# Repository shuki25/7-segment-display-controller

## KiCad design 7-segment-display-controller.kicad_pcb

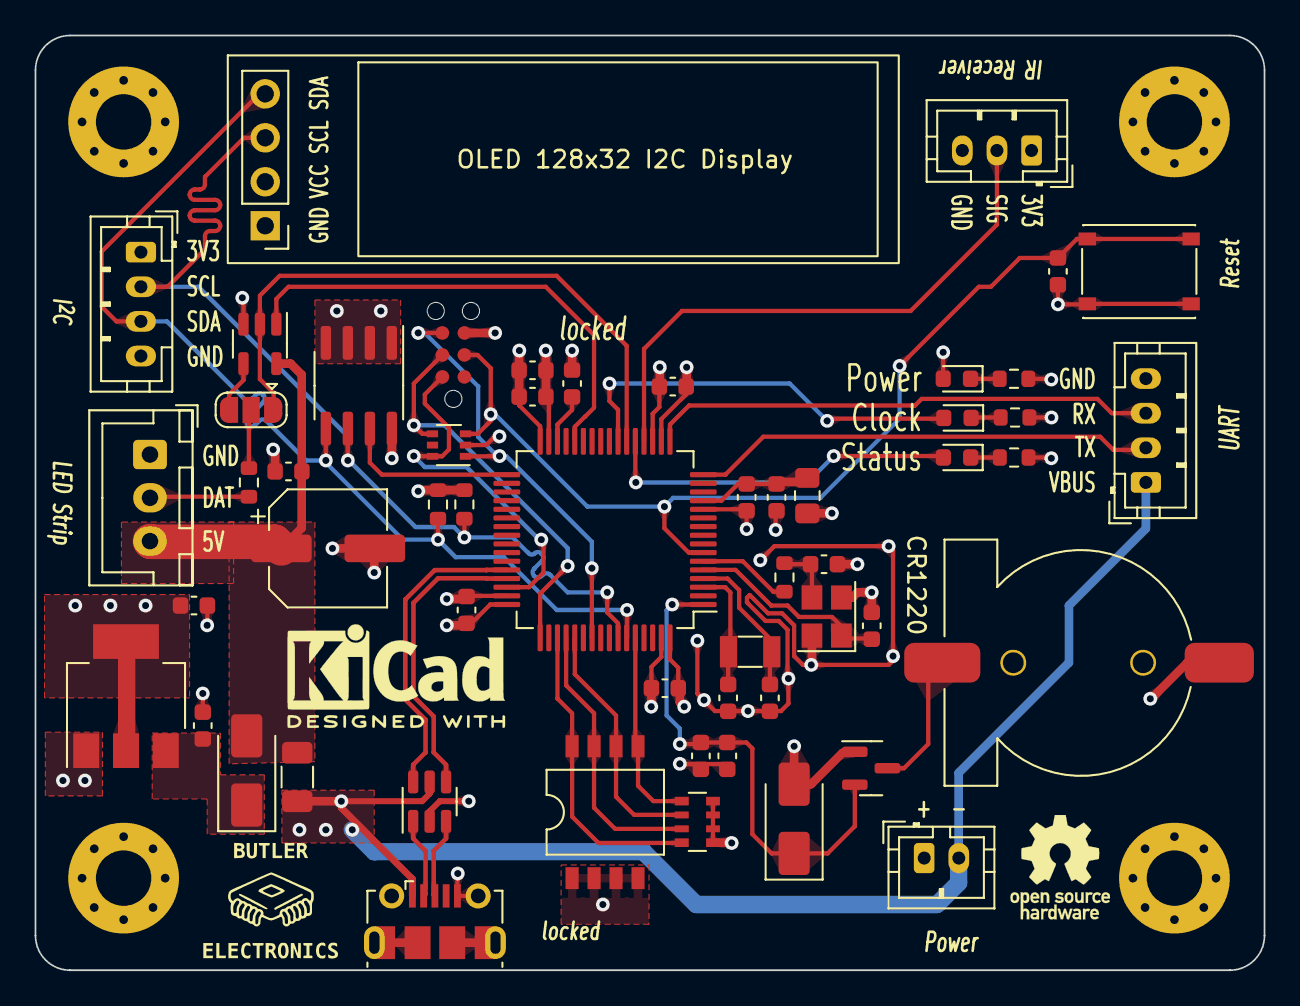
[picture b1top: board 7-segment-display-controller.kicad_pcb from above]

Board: 4 copper layers, 71.0 x 54.0 mm, 59 parts (0 on the bottom side), 42 nets.

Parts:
BT101: Battery_Cell; BatteryHolder_CR1220
C101, C107: 1uF; C_0603_1608Metric
C102, C117: 4.7uF; C_0603_1608Metric
C103, C104, C105, C106, C111, C114, C116, C118: 100nF; C_0603_1608Metric
C108, C109: 10pF; C_0603_1608Metric
C112, C113: 15pF; C_0603_1608Metric
C115: 470uF; CP_Elec_6.3x7.7
C201, C202: 22uF; C_0603_1608Metric
D101: GREEN; LED_0603_1608Metric
D102: RED; LED_0603_1608Metric
D103, D106: SS34; D_SMA
D104: SP0505BAJT; SOT-363_SC-70-6
D107: BLUE; LED_0603_1608Metric
F101: Polyfuse_Small; Fuse_1206_3216Metric
FB101: 600@100MHz; L_0805_2012Metric_Pad1.15x1.40mm_HandSolder
H101, H102, H103, H104: MountingHole; MountingHole_3.2mm_M3_Pad_Via
J101: Tag Connector; TC2030-IDC-NL
J102: USB_B_Micro; USB_Micro-B_Molex-105017-0001
J103, J105: JST 2.54 Header; JST_PH_B4B-PH-K_1x04_P2.00mm_Vertical
J104: JST 2.54 Header; JST_XH_B3B-XH-A_1x03_P2.50mm_Vertical
J106: JST 2.54 Header; JST_PH_B3B-PH-K_1x03_P2.00mm_Vertical
J107: Conn_01x02; JST_PH_B2B-PH-K_1x02_P2.00mm_Vertical
OLED101: OLED_I2C; OLED_128x32_I2C_4pins
Q101: AO3501A; SOT-23
R101, R105: 2K2; R_0603_1608Metric
R102, R109, R110: 1K5; R_0603_1608Metric
R103: 0; R_0603_1608Metric
R104: 330; R_0603_1608Metric
RN101: 10K; R_Array_Convex_4x0603
SW101: SW_DIP_x04; SMDIP-8_W6.6mm
SW106: SW_Push; XKB-Connectivity-TS-1187A-B-A-B
SW107: SW_SPDT; SolderJumper-3_P1.3mm_Open_RoundedPad1.0x1.5mm
U101: STM32F401RCTx; LQFP-64_10x10mm_P0.5mm
U102: USBLC6-2SC6; SOT-23-6
U103: 74AHCT1G125; SOT-23-5
U104: M24C64-RMN; SOIC-8_3.9x4.9mm_P1.27mm
U201: AMS1117-3.3; SOT-223-3_TabPin2
Y101: 16MHz; Crystal_SMD_3225-4Pin_3.2x2.5mm
Y103: 32.768kHz; Crystal_SMD_3215-2Pin_3.2x1.5mm

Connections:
+3.3VA: C106.1, C107.1, FB101.1, U101.13 (VREF+)
+3V3: C102.1, C103.1, C104.1, C105.1, C111.1, C202.2, D102.2 (A), D106.2 (A), FB101.2, J105.1, J106.1, OLED101.2 (VCC), Q101.1 (G), R109.2, R110.2, SW101.1, SW101.2, SW101.3, SW101.4, U101.19 (VDD), U101.32 (VDD), U101.48 (VDD), U101.64 (VDD), U104.8 (VCC), U201.2 (VO)
+5V: C115.1, C118.1, D103.2 (A), F101.2, J104.3, U103.5 (VCC)
/BAT+: BT101.1 (+), Q101.3 (D)
/BOOT0: RN101.5 (R4.2), SW101.5, U101.60 (BOOT0)
/DIP1: RN101.6 (R3.2), SW101.6, U101.53 (PC12)
/DIP2: RN101.7 (R2.2), SW101.7, U101.52 (PC11)
/DIP3: RN101.8 (R1.2), SW101.8, U101.51 (PC10)
/D_N: U101.44 (PA11), U102.6 (I/O1)
/D_P: U101.45 (PA12), U102.4 (I/O2)
/HSE_IN: C108.1, U101.5 (PH0), Y101.1
/HSE_OUT: R103.1, U101.6 (PH1)
/IR_RECV: J106.2, U101.20 (PA4)
/LDO_3V3/5V: C201.2, D103.1 (K), U201.3 (VI)
/LED_HB: D101.2 (A), U101.23 (PA7)
/LED_UI: D107.2 (A), U101.21 (PA5)
/LSE_IN: C112.2, U101.3 (PC14), Y103.2
/LSE_OUT: C113.2, U101.4 (PC15), Y103.1
/NRST: C114.1, D104.3 (K), J101.3, SW106.1, U101.7 (NRST)
/RGB_LED: SW107.1 (A), U101.22 (PA6), U103.2
/SCL: J105.2, OLED101.3 (SCL), R110.1, U101.58 (PB6), U104.6 (SCL)
/SDA: J105.3, OLED101.4 (SDA), R109.1, U101.59 (PB7), U104.5 (SDA)
/SWCLK: D104.4 (K), J101.4, U101.49 (PA14)
/SWDIO: D104.6 (K), J101.2, U101.46 (PA13)
/SWO: D104.1 (K), J101.6, U101.55 (PB3)
/UART_RX: J103.3, U101.17 (PA3)
/UART_TX: J103.2, U101.16 (PA2)
/USB_D_N: J102.2 (D-), U102.1 (I/O1)
/USB_D_P: J102.3 (D+), U102.3 (I/O2)
/VBAT: C101.1, C116.1, D106.1 (K), Q101.2 (S), U101.1 (VBAT)
/~EEPROM: U101.33 (PB12), U104.7 (~WC)
/~OE: U101.28 (PB2), U103.1
GND: BT101.2 (-), C101.2, C102.2, C103.2, C104.2, C105.2, C106.2, C107.2, C108.2, C109.2, C111.2, C112.1, C113.1, C114.2, C115.2, C116.2, C117.2, C118.2, C201.1, C202.1, D104.2 (A), H101.1, H102.1, H103.1, H104.1, J101.5, J102.5 (GND), J102.6 (Shield), J103.4, J104.1, J105.4, J106.3, J107.1, OLED101.1 (GND), R101.2, R102.2, R105.2, RN101.1 (R1.1), RN101.2 (R2.1), RN101.3 (R3.1), RN101.4 (R4.1), SW106.2, U101.12 (VSSA), U101.18 (VSS), U101.31 (VSS), U101.47 (VSS), U101.63 (VSS), U102.2 (GND), U103.3 (GND), U104.1 (E0), U104.2 (E1), U104.3 (E2), U104.4 (VSS), U201.1 (GND), Y101.2, Y101.4
unnamed: C109.1, R103.2, Y101.3
unnamed: D101.1 (K), R101.1
unnamed: D102.1 (K), R102.1
unnamed: D107.1 (K), R105.1
unnamed: J104.2, R104.1
unnamed: R104.2, SW107.2 (B)
unnamed: SW107.3 (C), U103.4
unnamed: C117.1, U101.30 (VCAP1)
VBUS: F101.1, J102.1 (VBUS), J103.1, J107.2, U102.5 (VBUS)

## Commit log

2023-05-16 update production files
2023-05-26 add alternate power source connector
2023-06-01 add 32.768KHz crystal
2023-06-01 update uuid
2023-06-02 fix crystal pin assignments
2023-06-06 add image and 3D model
2023-06-06 switch MCU to STM32F401
    - switch MCU to STM32F401 because STM32F303 does not have DMA stream
    - add EEPROM
    - removed D+ pull-up resistor
    - switch status LED to blue, changed resistor values
2023-06-06 update BOM
2023-06-14 add pdf plots
2023-06-27 update net color and schematic notes
2023-11-20 update schematic pdf
